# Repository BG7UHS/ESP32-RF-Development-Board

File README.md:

# ESP32-RF-Development-Board
esp32-pico-d4、cc1101、nrf24、sd、ip5306
Compatible with EvilCrow-RFv2 firmware
We do not guarantee normal work and assume no responsibility.

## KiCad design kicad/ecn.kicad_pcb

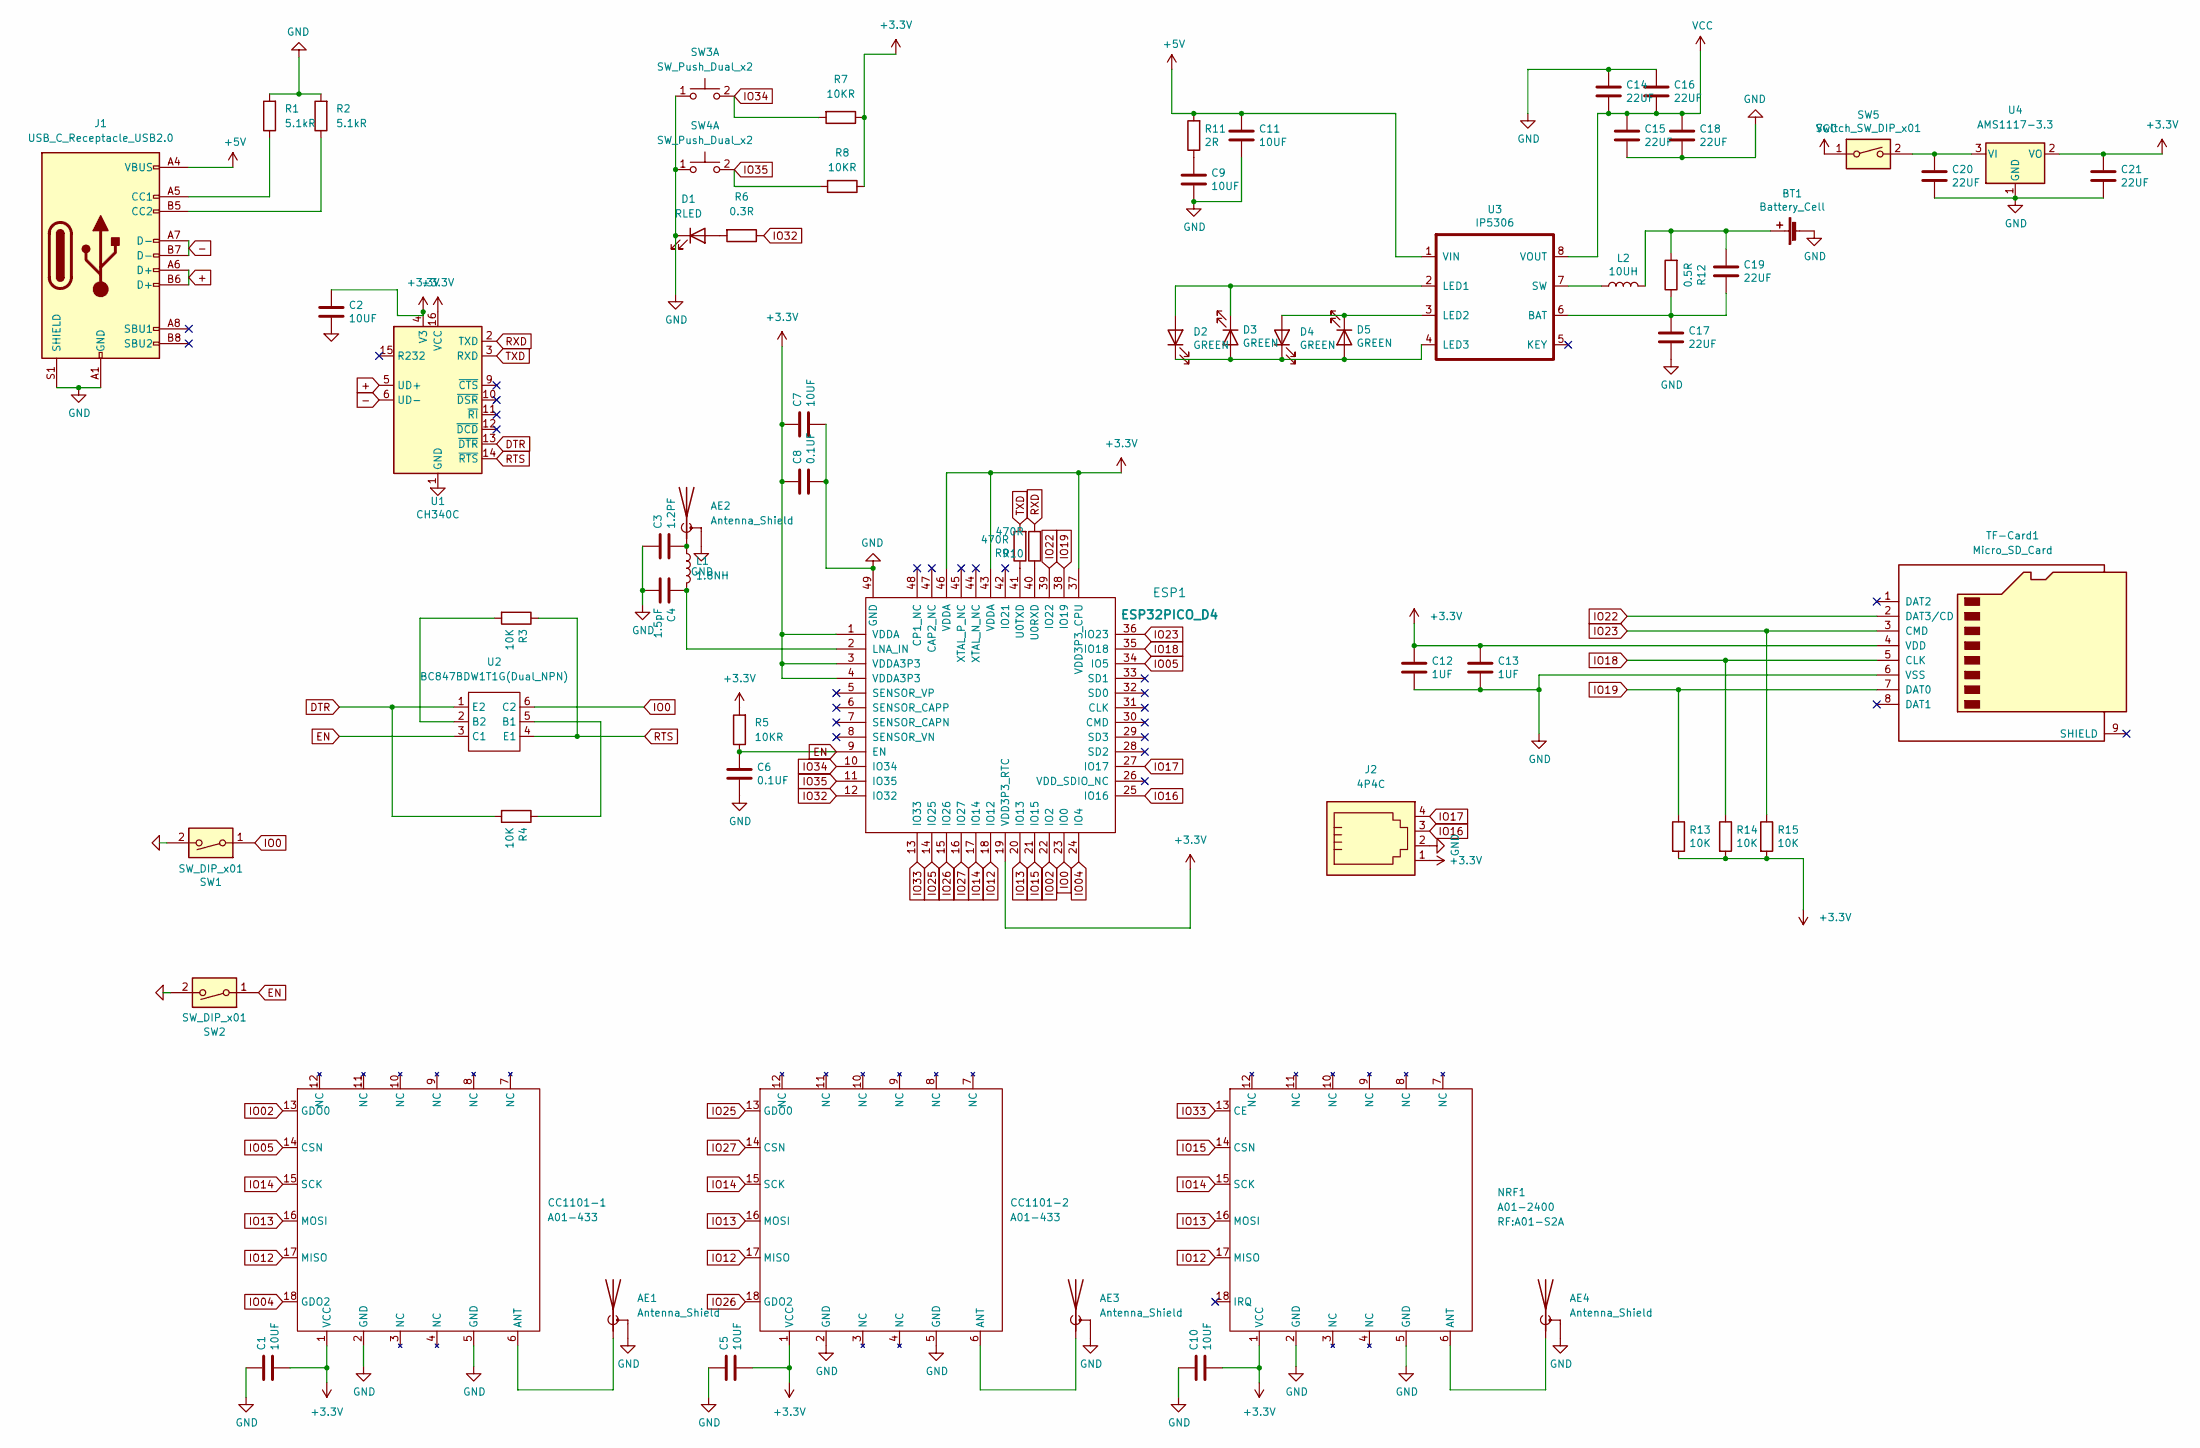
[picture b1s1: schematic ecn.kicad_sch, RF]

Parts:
AE1, AE3, AE4: Antenna_Shield; SMA-EDGE
AE2: Antenna_Shield; Texas_SWRA117D_2.4GHz_Right
BT1: Battery_Cell; JST_PH_S2B-PH-SM4-TB_02x2.00mm_Angled
C1, C2, C5, C7, C9, C10, C11: 10UF; C_0603_1608Metric
C3: 1.2PF; C_0603_1608Metric
C4: 1.5pF; C_0603_1608Metric
C6, C8: 0.1UF; C_0603_1608Metric
C12, C13: 1UF; C_0603_1608Metric
C14, C15, C16, C17, C18, C19, C20, C21: 22UF; C_0603_1608Metric
CC1101-1, CC1101-2: A01-433; A01-S2A
D1: RLED; D_0603_1608Metric
D2, D3, D4, D5: GREEN; LED_0603_1608Metric
ESP1: ESP32PICO_D4; QFN-48_L7.0-W7.0-P0.50-BL-EP5.4
J1: USB_C_Receptacle_USB2.0; USB_C_Receptacle_HRO_TYPE-C-31-M-12
J2: 4P4C; PinHeader_1x04_P2.54mm_Vertical
L1: 1.8NH; L_0603_1608Metric
L2: 10UH; L_Coilcraft_XxL4040
NRF1: A01-2400; A01-S2A
R1, R2: 5.1kR; R_0603_1608Metric
R3, R4, R13, R14, R15: 10K; R_0603_1608Metric
R5, R7, R8: 10KR; R_0603_1608Metric
R6: 0.3R; R_0603_1608Metric
R9, R10: 470R; R_0603_1608Metric
R11: 2R; R_0603_1608Metric
R12: 0.5R; R_0603_1608Metric
SW1, SW2: SW_DIP_x01; SW_SPST_FSMSM
SW3, SW4: SW_Push_Dual_x2; SW_SPST_TL3342
SW5: Switch_SW_DIP_x01; SW_SPDT_CK-JS102011SAQN
TF-Card1: Micro_SD_Card; microSD_HC_Molex_104031-0811
U1: CH340C; SOIC-16_3.9x9.9mm_P1.27mm
U2: BC847BDW1T1G(Dual_NPN); SOT-363_SC-70-6_Handsoldering
U3: IP5306; HSOP-8-1EP_3.9x4.9mm_P1.27mm_EP2.41x3.1mm
U4: AMS1117-3.3; SOT-223-3_TabPin2

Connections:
+: J1.A6 (D+), J1.B6 (D+), U1.5 (UD+)
+3V3: C1.2, C2.1, C5.2, C7.1, C8.1, C10.2, C12.1, C13.1, C21.1, CC1101-1.1 (VCC), CC1101-2.1 (VCC), ESP1.1 (VDDA), ESP1.3 (VDDA3P3), ESP1.4 (VDDA3P3), ESP1.19 (VDD3P3_RTC), ESP1.37 (VDD3P3_CPU), ESP1.43 (VDDA), ESP1.46 (VDDA), J2.1, NRF1.1 (VCC), R5.2, R7.1, R8.1, R13.2, R14.2, R15.2, TF-Card1.4 (VDD), U1.4 (V3), U1.16 (VCC), U4.2 (VO)
+5V: C11.1, J1.A4 (VBUS), J1.A9 (VBUS), J1.B4 (VBUS), J1.B9 (VBUS), R11.2, U3.1 (VIN)
-: J1.A7 (D-), J1.B7 (D-), U1.6 (UD-)
DTR: R4.2, U1.13 (~DTR), U2.1 (E2)
EN: C6.1, ESP1.9 (EN), R5.1, SW2.1, U2.3 (C1)
GND: AE1.2 (Shield), AE2.2 (Shield), AE3.2 (Shield), AE4.2 (Shield), BT1.2 (-), C1.1, C2.2, C3.1, C4.2, C5.1, C6.2, C7.2, C8.2, C9.2, C10.1, C11.2, C12.2, C13.2, C14.1, C15.2, C16.1, C17.2, C18.2, C20.2, C21.2, CC1101-1.2 (GND), CC1101-1.5 (GND), CC1101-2.2 (GND), CC1101-2.5 (GND), D1.1 (K), ESP1.0, ESP1.49 (GND), J1.A1 (GND), J1.A12 (GND), J1.B1 (GND), J1.B12 (GND), J1.S1 (SHIELD), J2.2, NRF1.2 (GND), NRF1.5 (GND), R1.2, R2.2, SW1.2, SW2.2, SW3.1 (C), SW4.1 (C), TF-Card1.6 (VSS), U1.1 (GND), U4.1 (GND)
IO0: ESP1.23 (IO0), SW1.1, U2.6 (C2)
IO02: CC1101-1.13 (GDO0), ESP1.22 (IO2)
IO04: CC1101-1.18 (GDO2), ESP1.24 (IO4)
IO05: CC1101-1.14 (CSN), ESP1.34 (IO5)
IO12: CC1101-1.17 (MISO), CC1101-2.17 (MISO), ESP1.18 (IO12), NRF1.17 (MISO)
IO13: CC1101-1.16 (MOSI), CC1101-2.16 (MOSI), ESP1.20 (IO13), NRF1.16 (MOSI)
IO14: CC1101-1.15 (SCK), CC1101-2.15 (SCK), ESP1.17 (IO14), NRF1.15 (SCK)
IO15: ESP1.21 (IO15), NRF1.14 (CSN)
IO16: ESP1.25 (IO16), J2.3
IO17: ESP1.27 (IO17), J2.4
IO18: ESP1.35 (IO18), R14.1, TF-Card1.5 (CLK)
IO19: ESP1.38 (IO19), R13.1, TF-Card1.7 (DAT0)
IO22: ESP1.39 (IO22), TF-Card1.2 (DAT3/CD)
IO23: ESP1.36 (IO23), R15.1, TF-Card1.3 (CMD)
IO25: CC1101-2.13 (GDO0), ESP1.14 (IO25)
IO26: CC1101-2.18 (GDO2), ESP1.15 (IO26)
IO27: CC1101-2.14 (CSN), ESP1.16 (IO27)
IO32: ESP1.12 (IO32), R6.1
IO33: ESP1.13 (IO33), NRF1.13 (CE)
IO34: ESP1.10 (IO34), R7.2, SW3.2 (D)
IO35: ESP1.11 (IO35), R8.2, SW4.2 (D)
unnamed: AE1.1 (A), CC1101-1.6 (ANT)
unnamed: AE2.1 (A), C3.2, L1.1
unnamed: AE3.1 (A), CC1101-2.6 (ANT)
unnamed: AE4.1 (A), NRF1.6 (ANT)
unnamed: BT1.1 (+), C19.1, L2.2, R12.2
unnamed: C4.1, ESP1.2 (LNA_IN), L1.2
unnamed: C9.1, R11.1
unnamed: C17.1, C19.2, R12.1, U3.6 (BAT)
unnamed: C20.1, SW5.2, U4.3 (VI)
unnamed: D1.2 (A), R6.2
unnamed: D2.1 (K), D3.2 (A), D4.1 (K), D5.2 (A), U3.4 (LED3)
unnamed: D2.2 (A), D3.1 (K), U3.2 (LED1)
unnamed: D4.2 (A), D5.1 (K), U3.3 (LED2)
unnamed: ESP1.40 (U0RXD), R10.1
unnamed: ESP1.41 (U0TXD), R9.1
unnamed: J1.A5 (CC1), R1.1
unnamed: J1.B5 (CC2), R2.1
unnamed: L2.1, U3.7 (SW)
unnamed: R3.2, U2.2 (B2)
unnamed: R4.1, U2.5 (B1)
RTS: R3.1, U1.14 (~RTS), U2.4 (E1)
RXD: R10.2, U1.2 (TXD)
TXD: R9.2, U1.3 (RXD)
VCC: C14.2, C15.1, C16.2, C18.1, SW5.1, U3.8 (VOUT)

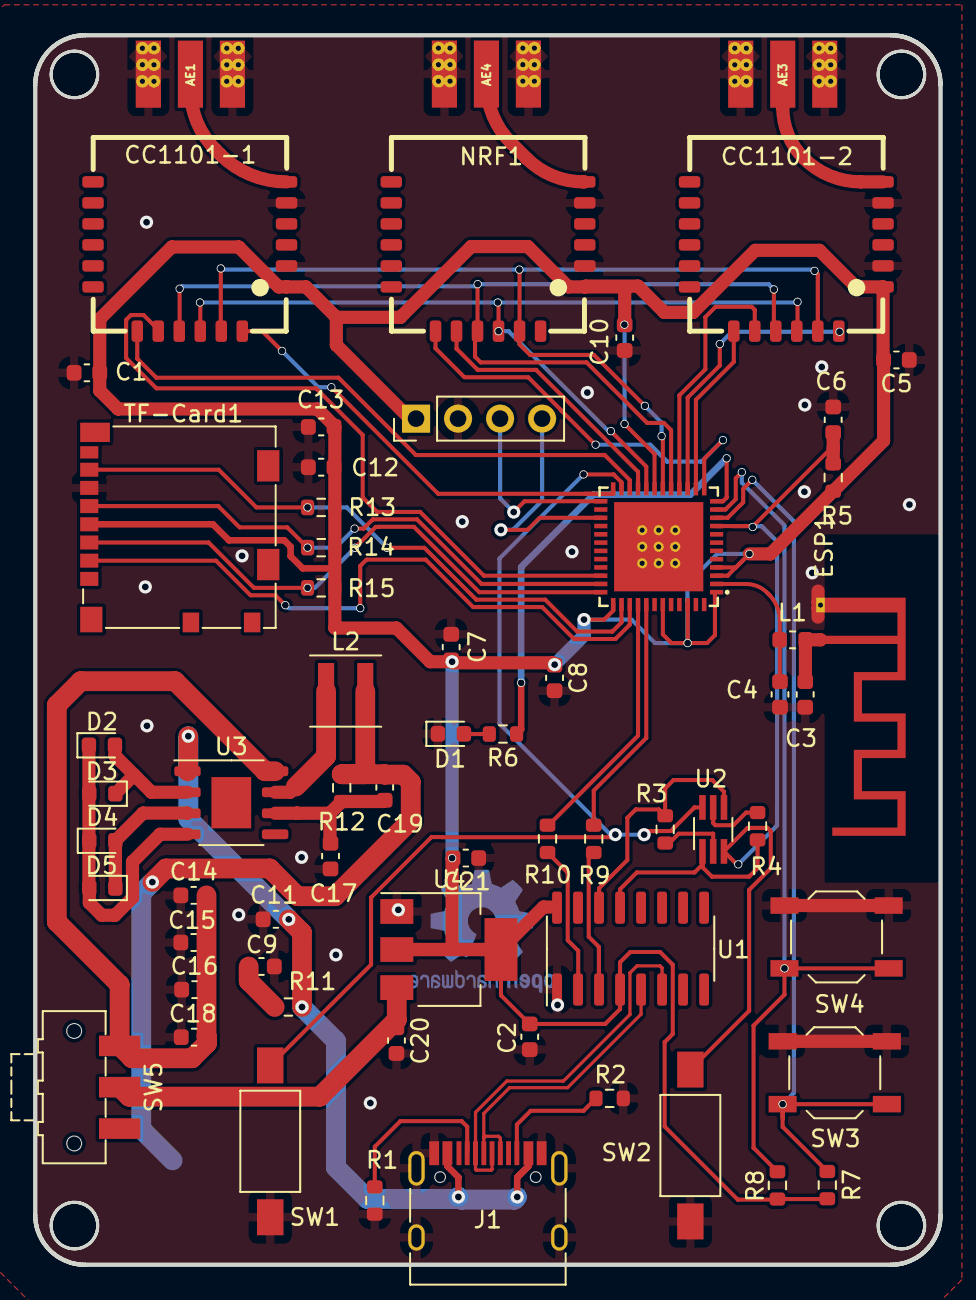
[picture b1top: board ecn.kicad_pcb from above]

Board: 2 copper layers, 54.7 x 74.3 mm, 64 parts (1 on the bottom side), 52 nets.
